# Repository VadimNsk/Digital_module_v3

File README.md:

# Digital_module_v3
Цифровой модуль управления

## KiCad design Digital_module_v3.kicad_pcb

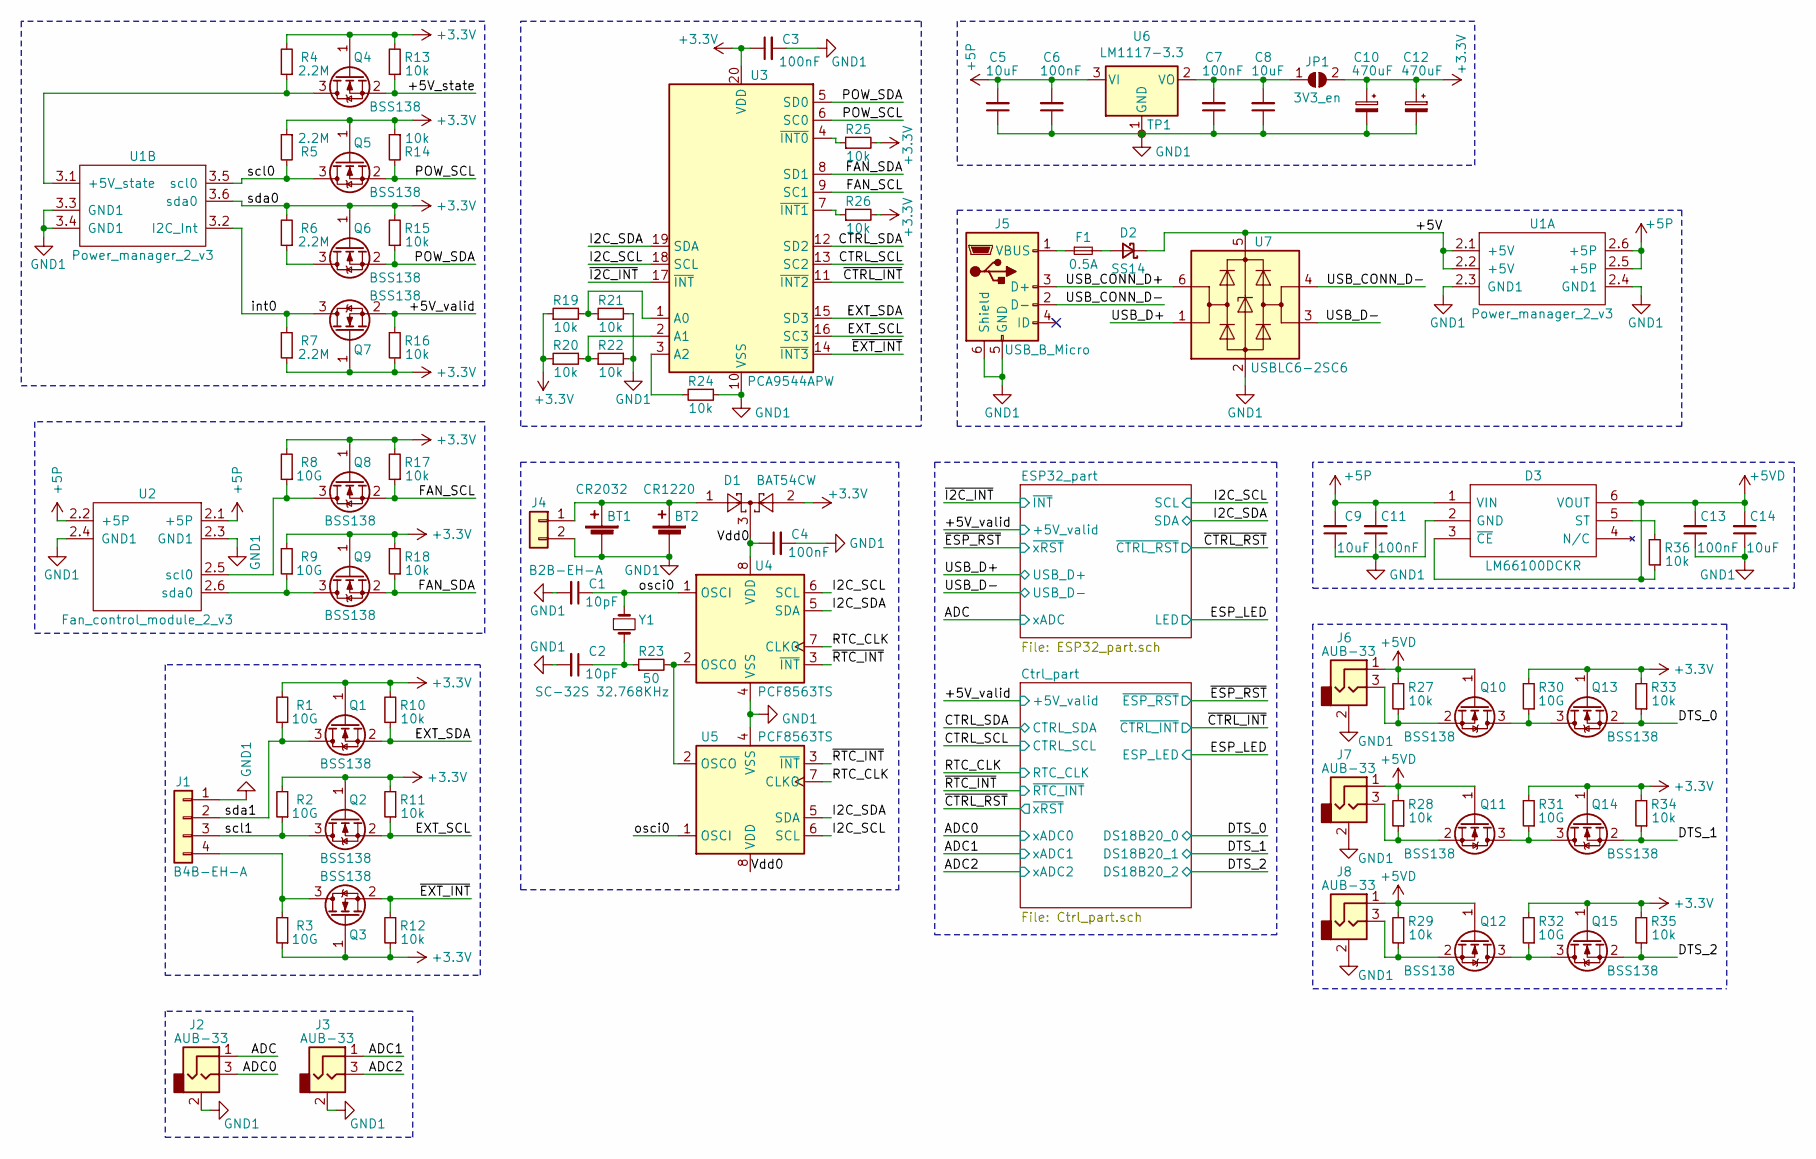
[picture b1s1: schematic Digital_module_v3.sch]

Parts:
BT1: CR2032; CR2032BS51
BT2: CR1220; CR1220HSMD
C1, C2: 10pF; C_0603_1608Metric
C3, C4, C6, C7, C11, C13: 100nF; C_0603_1608Metric
C5, C8, C9, C14: 10uF; C_0603_1608Metric
C10, C12: 470uF; CP_EIA-7343-31_Kemet-D
D1: BAT54CW; SOT-323_SC-70
D2: SS14; D_SMA
D3: LM66100DCKR; SOP65P210X110-6N; Manufacturer_Part_Number LM66100DCKR; Mouser Part Number 595-LM66100DCKR
F1: 0.5A; Fuse_1206_3216Metric
J1: B4B-EH-A; JST_EH_S4B-EH_1x04_P2.50mm_Horizontal
J2, J3, J6, J7, J8: AUB-33
J4: B2B-EH-A; JST_EH_S2B-EH_1x02_P2.50mm_Horizontal
J5: USB_B_Micro; USB_Micro-B_Wuerth_629105150521
JP1: 3V3_en; SolderJumper-2_P1.3mm_Open_TrianglePad1.0x1.5mm
Q1, Q2, Q3, Q4, Q5, Q6, Q7, Q8, Q9, Q10, Q11, Q12, Q13, Q14, Q15: BSS138; SOT-23
R1, R2, R3, R8, R9, R30, R31, R32: 10G; R_0603_1608Metric
R4, R5, R6, R7: 2.2M; R_0603_1608Metric
R10, R11, R12, R13, R14, R15, R16, R17, R18, R19, R20, R21, R22, R24, R25, R26, R27, R28, R29, R33, R34, R35, R36: 10k; R_0603_1608Metric
R23: 50; R_0603_1608Metric
TP1: GND1; TestPoint_THTPad_D2.0mm_Drill1.0mm
U1: Power_manager_2_v3
U2: Fan_control_module_2_v3; Fan_controller_2_v3
U3: PCA9544APW; TSSOP-20_4.4x6.5mm_P0.65mm
U4: PCF8563TS; SOT65P490X110-8N
U5: PCF8563TS; SO-8_3.9x4.9mm_P1.27mm
U6: LM1117-3.3; SOT-223-3_TabPin2
U7: USBLC6-2SC6; SOT-23-6
Y1: SC-32S 32.768KHz; Crystal_SMD_3215-2Pin_3.2x1.5mm

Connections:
+3V3: C3.1, C10.1, C12.1, D1.2, JP1.2 (B), Q1.1 (G), Q2.1 (G), Q3.1 (G), Q4.1 (G), Q5.1 (G), Q6.1 (G), Q7.1 (G), Q8.1 (G), Q9.1 (G), Q13.1 (G), Q14.1 (G), Q15.1 (G), R1.2, R2.2, R3.1, R4.2, R5.1, R6.2, R7.1, R8.2, R9.2, R10.2, R11.2, R12.1, R13.2, R14.1, R15.2, R16.1, R17.2, R18.2, R19.1, R20.1, R25.2, R26.2, R30.2, R31.2, R32.2, R33.2, R34.2, R35.2, U1.3.6 (sda0), U3.20 (VDD); also elsewhere on the board
+5P: C5.2, C6.2, C9.2, C11.2, D3.1 (VIN), U1.2.5 (+5P), U1.2.6 (+5P), U2.2.1 (+5P), U2.2.2 (+5P), U6.3 (VI); also elsewhere on the board
+5VD: C13.2, C14.2, D3.3 (~CE), D3.6 (VOUT), J6.1, J7.1, J8.1, Q10.1 (G), Q11.1 (G), Q12.1 (G), R27.2, R28.2, R29.2, R36.1
/+5V: D2.1 (K), U1.2.1 (+5V), U1.2.2 (+5V), U7.5 (VBUS)
/+5V_state: Q4.2 (S), R13.1
/+5V_valid: Q7.2 (S), R16.2; also elsewhere on the board
/ADC: J2.1; also elsewhere on the board
/ADC0: J2.3; also elsewhere on the board
/ADC1: J3.1; also elsewhere on the board
/ADC2: J3.3; also elsewhere on the board
/CTRL_SCL: U3.13 (SC2); also elsewhere on the board
/CTRL_SDA: U3.12 (SD2); also elsewhere on the board
/DTS_0: Q13.2 (S), R33.1; also elsewhere on the board
/DTS_1: Q14.2 (S), R34.1; also elsewhere on the board
/DTS_2: Q15.2 (S), R35.1; also elsewhere on the board
/EXT_SCL: Q2.2 (S), R11.1, U3.16 (SC3)
/EXT_SDA: Q1.2 (S), R10.1, U3.15 (SD3)
/FAN_SCL: Q8.2 (S), R17.1, U3.9 (SC1)
/FAN_SDA: Q9.2 (S), R18.1, U3.8 (SD1)
/I2C_SCL: U3.18 (SCL), U4.6 (SCL), U5.6 (SCL); also elsewhere on the board
/I2C_SDA: U3.19 (SDA), U4.5 (SDA), U5.5 (SDA); also elsewhere on the board
/POW_SCL: Q5.2 (S), R14.2, U3.6 (SC0)
/POW_SDA: Q6.2 (S), R15.1, U3.5 (SD0)
/RTC_CLK: U4.7 (CLKO), U5.7 (CLKO); also elsewhere on the board
/USB_CONN_D+: J5.3 (D+), U7.6 (I/O1)
/USB_CONN_D-: J5.2 (D-), U7.4 (I/O2)
/USB_D+: U7.1 (I/O1); also elsewhere on the board
/USB_D-: U7.3 (I/O2); also elsewhere on the board
/Vdd0: C4.1, D1.3, U4.8 (VDD), U5.8 (VDD)
/int0: Q7.3 (D), R7.2, U1.3.2 (I2C_Int)
/osci0: C1.1, U4.1 (OSCI), U5.1 (OSCI), Y1.1
/scl0: Q5.3 (D), R5.2, U1.3.5 (scl0)
/scl1: J1.3, Q2.3 (D), R2.1
/sda1: J1.2, Q1.3 (D), R1.1
/~CTRL_INT: U3.11 (~INT2); also elsewhere on the board
/~EXT_INT: Q3.2 (S), R12.2, U3.14 (~INT3)
/~I2C_INT: U3.17 (~INT); also elsewhere on the board
/~RTC_INT: U4.3 (~INT~), U5.3 (~INT~); also elsewhere on the board
GND1: BT1.2 (-), BT2.2 (-), C1.2, C2.2, C3.2, C4.2, C5.1, C6.1, C7.1, C8.1, C9.1, C10.2, C11.1, C12.2, C13.1, C14.1, D3.2 (GND), J1.1, J2.2, J3.2, J4.2, J5.5 (GND), J5.6 (Shield), J6.2, J7.2, J8.2, R21.2, R22.2, R24.1, TP1.1, U1.2.3 (GND1), U1.2.4 (GND1), U1.3.3 (GND1), U1.3.4 (GND1), U2.2.3 (GND1), U2.2.4 (GND1), U3.10 (VSS), U4.4 (VSS), U5.4 (VSS), U6.1 (GND), U7.2 (GND); also elsewhere on the board
unnamed: BT1.1 (+), BT2.1 (+), D1.1, J4.1
unnamed: C2.1, R23.1, Y1.2
unnamed: C7.2, C8.2, JP1.1 (A), U6.2 (VO)
unnamed: D2.2 (A), F1.2
unnamed: D3.5 (ST), R36.2
unnamed: F1.1, J5.1 (VBUS)
unnamed: J1.4, Q3.3 (D), R3.2
unnamed: J6.3, Q10.2 (S), R27.1
unnamed: J7.3, Q11.2 (S), R28.1
unnamed: J8.3, Q12.2 (S), R29.1
unnamed: Q4.3 (D), R4.1, U1.3.1 (+5V_state)
unnamed: Q6.3 (D), R6.1
unnamed: Q8.3 (D), R8.1, U2.2.5 (scl0)
unnamed: Q9.3 (D), R9.1, U2.2.6 (sda0)
unnamed: Q10.3 (D), Q13.3 (D), R30.1
unnamed: Q11.3 (D), Q14.3 (D), R31.1
unnamed: Q12.3 (D), Q15.3 (D), R32.1
unnamed: R19.2, R21.1, U3.1 (A0)
unnamed: R20.2, R22.1, U3.2 (A1)
unnamed: R23.2, U4.2 (OSCO), U5.2 (OSCO)
unnamed: R24.2, U3.3 (A2)
unnamed: R25.1, U3.4 (~INT0)
unnamed: R26.1, U3.7 (~INT1)

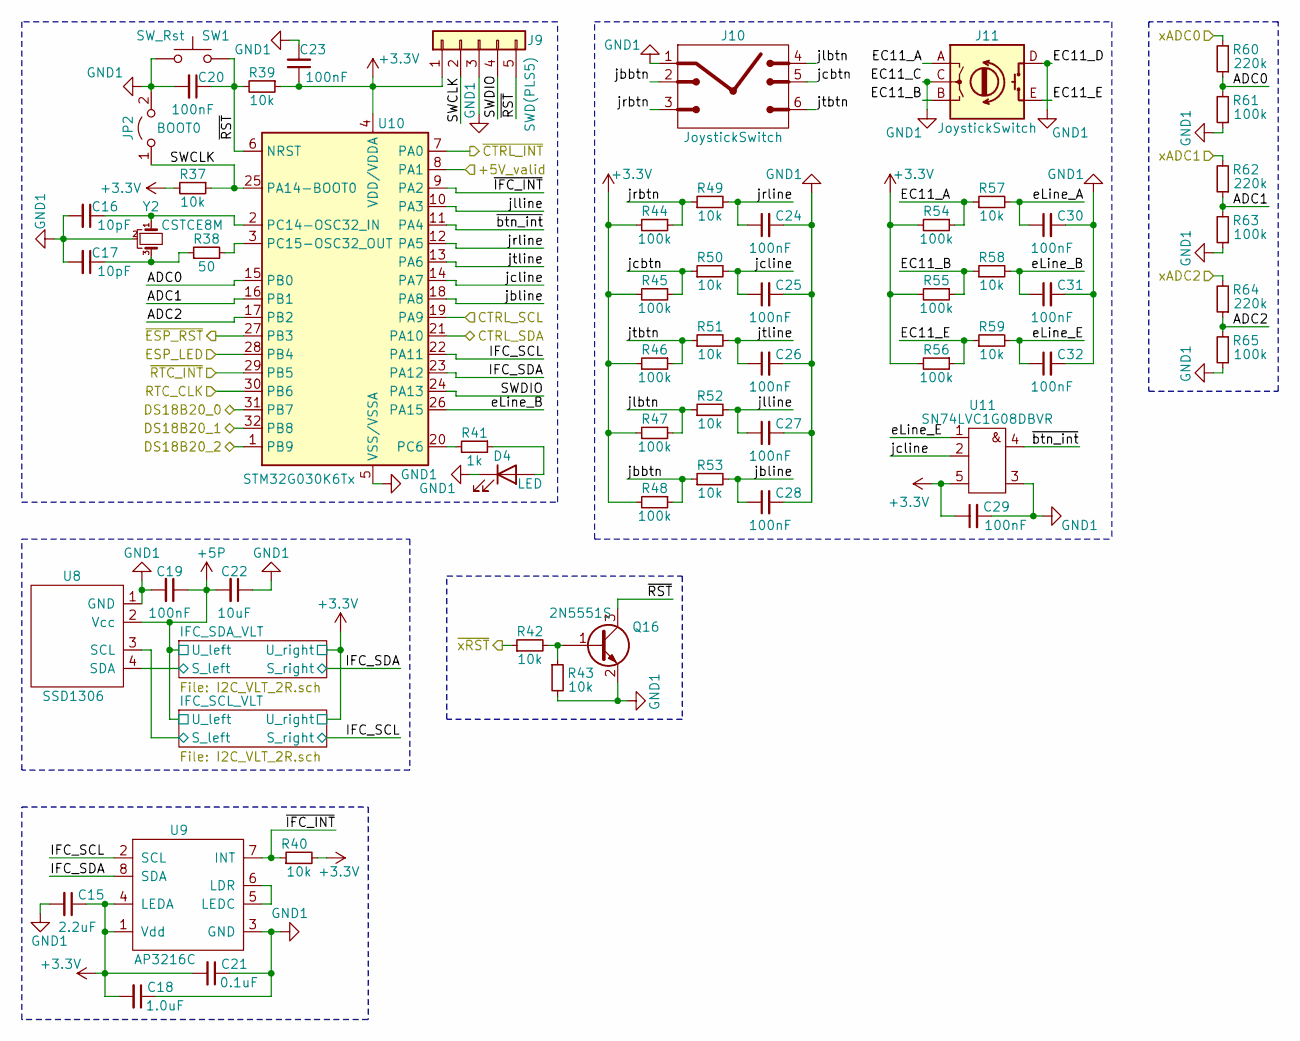
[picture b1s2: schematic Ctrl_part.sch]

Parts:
C15: 2.2uF; C_0603_1608Metric
C16, C17: 10pF; C_0603_1608Metric
C18: 1.0uF; C_0603_1608Metric
C19, C20, C23, C24, C25, C26, C27, C28, C29, C30, C31, C32: 100nF; C_0603_1608Metric
C21: 0.1uF; C_0603_1608Metric
C22: 10uF; C_0603_1608Metric
D4: LED; LED_0603_1608Metric
J9: SWD(PLS5); PinSocket_1x05_P1.27mm_Vertical_SMD_Pin1Left
J10: JoystickSwitch
J11: JoystickSwitch; EC11_SMD
JP2: BOOT0; PinHeader_1x02_P1.27mm_Vertical
Q16: 2N5551S; SOT-23
R37, R39, R40, R42, R43, R49, R50, R51, R52, R53, R57, R58, R59: 10k; R_0603_1608Metric
R38: 50; R_0603_1608Metric
R41: 1k; R_0603_1608Metric
R44, R45, R46, R47, R48, R54, R55, R56, R61, R63, R65: 100k; R_0603_1608Metric
R60, R62, R64: 220k; R_0603_1608Metric
SW1: SW_Rst; SW_SPST_EVQP7C
U8: SSD1306; SSD1306_2_I2C
U9: AP3216C
U10: STM32G030K6Tx; LQFP-32_7x7mm_P0.8mm
U11: SN74LVC1G08DBVR; SOT-23-5
Y2: CSTCE8M; Resonator_SMD_muRata_CSTxExxV-3Pin_3.0x1.1mm_HandSoldering

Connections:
+3V3: C15.1, C18.2, C21.2, C23.1, C29.1, J9.1, R37.2, R39.1, R40.2, R44.2, R45.2, R46.2, R47.2, R48.2, R54.2, R55.2, R56.2, U9.1 (Vdd), U9.4 (LEDA), U10.4 (VDD/VDDA), U11.5 (VCC); also elsewhere on the board
+5P: C19.1, C22.2, U8.2 (Vcc); also elsewhere on the board
/+5V_valid: U10.8 (PA1); also elsewhere on the board
/ADC0: R60.2; also elsewhere on the board
/ADC1: R62.2; also elsewhere on the board
/ADC2: R64.2; also elsewhere on the board
/CTRL_SCL: U10.19 (PA9); also elsewhere on the board
/CTRL_SDA: U10.21 (PA10); also elsewhere on the board
/Ctrl_part/ADC0: R60.1, R61.2, U10.15 (PB0)
/Ctrl_part/ADC1: R62.1, R63.2, U10.16 (PB1)
/Ctrl_part/ADC2: R64.1, R65.2, U10.17 (PB2)
/Ctrl_part/EC11_A: J11.A, R54.1, R57.1
/Ctrl_part/EC11_B: J11.B, R55.1, R58.1
/Ctrl_part/EC11_E: J11.E, R56.1, R59.1
/Ctrl_part/IFC_SCL: U9.2 (SCL), U10.22 (PA11); also elsewhere on the board
/Ctrl_part/IFC_SCL_VLT/S_left: U8.3 (SCL); also elsewhere on the board
/Ctrl_part/IFC_SDA: U9.8 (SDA), U10.23 (PA12); also elsewhere on the board
/Ctrl_part/IFC_SDA_VLT/S_left: U8.4 (SDA); also elsewhere on the board
/Ctrl_part/SWCLK: J9.2, JP2.1 (A), R37.1, U10.25 (PA14-BOOT0)
/Ctrl_part/SWDIO: J9.4, U10.24 (PA13)
/Ctrl_part/eLine_A: C30.1, R57.2
/Ctrl_part/eLine_B: C31.1, R58.2, U10.26 (PA15)
/Ctrl_part/eLine_E: C32.1, R59.2, U11.1
/Ctrl_part/jbbtn: J10.2, R48.1, R53.1
/Ctrl_part/jbline: C28.1, R53.2, U10.18 (PA8)
/Ctrl_part/jcbtn: J10.5, R45.1, R50.1
/Ctrl_part/jcline: C25.1, R50.2, U10.14 (PA7), U11.2
/Ctrl_part/jlbtn: J10.4, R47.1, R52.1
/Ctrl_part/jlline: C27.1, R52.2, U10.10 (PA3)
/Ctrl_part/jrbtn: J10.3, R44.1, R49.1
/Ctrl_part/jrline: C24.1, R49.2, U10.12 (PA5)
/Ctrl_part/jtbtn: J10.6, R46.1, R51.1
/Ctrl_part/jtline: C26.1, R51.2, U10.13 (PA6)
/Ctrl_part/~IFC_INT: R40.1, U9.7 (INT), U10.9 (PA2)
/Ctrl_part/~RST: C20.1, J9.5, Q16.3 (C), R39.2, SW1.2, U10.6 (NRST)
/Ctrl_part/~btn_int: U10.11 (PA4), U11.4
/DTS_0: U10.31 (PB7); also elsewhere on the board
/DTS_1: U10.32 (PB8); also elsewhere on the board
/DTS_2: U10.1 (PB9); also elsewhere on the board
/ESP_LED: U10.28 (PB4); also elsewhere on the board
/RTC_CLK: U10.30 (PB6); also elsewhere on the board
/~CTRL_INT: U10.7 (PA0); also elsewhere on the board
/~CTRL_RST: R42.1; also elsewhere on the board
/~ESP_RST: U10.27 (PB3); also elsewhere on the board
/~RTC_INT: U10.29 (PB5); also elsewhere on the board
GND1: C15.2, C16.2, C17.2, C18.1, C19.2, C20.2, C21.1, C22.1, C23.2, C24.2, C25.2, C26.2, C27.2, C28.2, C29.2, C30.2, C31.2, C32.2, D4.1 (K), J9.3, J10.1, J11.C, J11.D, JP2.2 (B), Q16.2 (E), R43.2, R61.1, R63.1, R65.1, SW1.1, U8.1 (GND), U9.3 (GND), U10.5 (VSS/VSSA), U11.3 (GND), Y2.2; also elsewhere on the board
unnamed: C16.1, U10.2 (PC14-OSC32_IN), Y2.1
unnamed: C17.1, R38.1, Y2.3
unnamed: D4.2 (A), R41.1
unnamed: Q16.1 (B), R42.2, R43.1
unnamed: R38.2, U10.3 (PC15-OSC32_OUT)
unnamed: R41.2, U10.20 (PC6)
unnamed: U9.5 (LEDC), U9.6 (LDR)

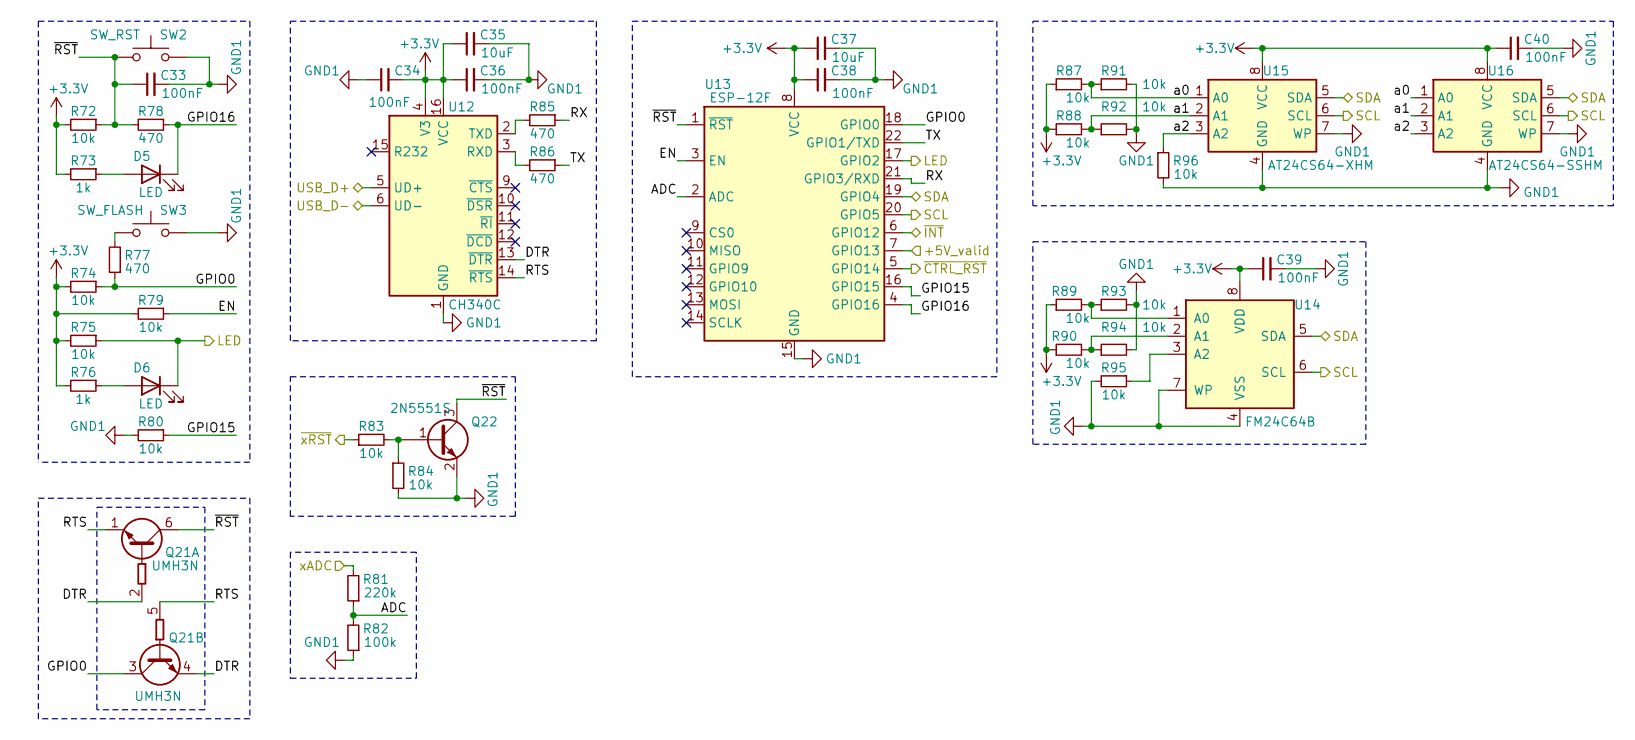
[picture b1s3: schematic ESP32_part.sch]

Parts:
C33, C34, C36, C38, C39, C40: 100nF; C_0603_1608Metric
C35, C37: 10uF; C_0603_1608Metric
D5, D6: LED; LED_0603_1608Metric
Q21: UMH3N; SOT-363_SC-70-6
Q22: 2N5551S; SOT-23
R72, R74, R75, R79, R80, R83, R84, R87, R88, R89, R90, R91, R92, R93, R94, R95, R96: 10k; R_0603_1608Metric
R73, R76: 1k; R_0603_1608Metric
R77, R78, R85, R86: 470; R_0603_1608Metric
R81: 220k; R_0603_1608Metric
R82: 100k; R_0603_1608Metric
SW2: SW_RST; SW_SPST_EVQP7C
SW3: SW_FLASH; SW_SPST_EVQP7C
U12: CH340C; SOIC-16_3.9x9.9mm_P1.27mm
U13: ESP-12F; ESP-12E
U14: FM24C64B; SOIC-8_3.9x4.9mm_P1.27mm
U15: AT24CS64-XHM; TSSOP-8_4.4x3mm_P0.65mm
U16: AT24CS64-SSHM; SOIC-8_3.9x4.9mm_P1.27mm

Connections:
+3V3: C34.2, C35.1, C36.1, C37.1, C38.1, C39.1, C40.1, R72.2, R73.2, R74.2, R75.2, R76.2, R79.2, R87.1, R88.1, R89.1, R90.1, U12.4 (V3), U12.16 (VCC), U13.8 (VCC), U14.8 (VDD), U15.8 (VCC), U16.8 (VCC); also elsewhere on the board
/+5V_valid: U13.7 (GPIO13); also elsewhere on the board
/ADC: R81.2; also elsewhere on the board
/ESP32_part/ADC: R81.1, R82.2, U13.2 (ADC)
/ESP32_part/DTR: Q21.2 (B1), Q21.4 (E2), U12.13 (~DTR)
/ESP32_part/EN: R79.1, U13.3 (EN)
/ESP32_part/GPIO0: Q21.3 (C2), R74.1, R77.1, U13.18 (GPIO0)
/ESP32_part/GPIO15: R80.1, U13.16 (GPIO15)
/ESP32_part/GPIO16: D5.1 (K), R78.1, U13.4 (GPIO16)
/ESP32_part/RTS: Q21.1 (E1), Q21.5 (B2), U12.14 (~RTS)
/ESP32_part/RX: R85.1, U13.21 (GPIO3/RXD)
/ESP32_part/TX: R86.1, U13.22 (GPIO1/TXD)
/ESP32_part/a0: R87.2, R91.1, U15.1 (A0), U16.1 (A0)
/ESP32_part/a1: R88.2, R92.1, U15.2 (A1), U16.2 (A1)
/ESP32_part/a2: R96.1, U15.3 (A2), U16.3 (A2)
/ESP32_part/~RST: C33.1, Q21.6 (C1), Q22.3 (C), R72.1, R78.2, SW2.1, U13.1 (~RST)
/ESP_LED: D6.1 (K), R75.1, U13.17 (GPIO2); also elsewhere on the board
/I2C_SCL: U13.20 (GPIO5), U14.6 (SCL), U15.6 (SCL), U16.6 (SCL); also elsewhere on the board
/I2C_SDA: U13.19 (GPIO4), U14.5 (SDA), U15.5 (SDA), U16.5 (SDA); also elsewhere on the board
/USB_D+: U12.5 (UD+); also elsewhere on the board
/USB_D-: U12.6 (UD-); also elsewhere on the board
/~CTRL_RST: U13.5 (GPIO14); also elsewhere on the board
/~ESP_RST: R83.1; also elsewhere on the board
/~I2C_INT: U13.6 (GPIO12); also elsewhere on the board
GND1: C33.2, C34.1, C35.2, C36.2, C37.2, C38.2, C39.2, C40.2, Q22.2 (E), R80.2, R82.1, R84.2, R91.2, R92.2, R93.2, R94.2, R95.2, R96.2, SW2.2, SW3.2, U12.1 (GND), U13.15 (GND), U14.4 (VSS), U14.7 (WP), U15.4 (GND), U15.7 (WP), U16.4 (GND), U16.7 (WP); also elsewhere on the board
unnamed: D5.2 (A), R73.1
unnamed: D6.2 (A), R76.1
unnamed: Q22.1 (B), R83.2, R84.1
unnamed: R77.2, SW3.1
unnamed: R85.2, U12.2 (TXD)
unnamed: R86.2, U12.3 (RXD)
unnamed: R89.2, R93.1, U14.1 (A0)
unnamed: R90.2, R94.1, U14.2 (A1)
unnamed: R95.1, U14.3 (A2)

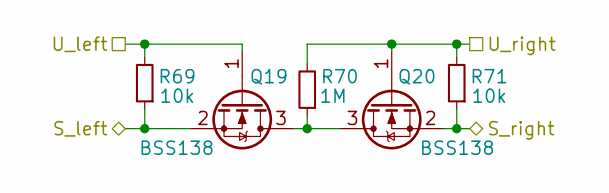
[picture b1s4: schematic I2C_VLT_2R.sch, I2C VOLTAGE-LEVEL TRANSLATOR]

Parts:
Q17, Q18: BSS138; SOT-23
R66, R68: 10k; R_0603_1608Metric
R67: 1M; R_0603_1608Metric

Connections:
+3V3: Q18.1 (G), R67.2, R68.2; also elsewhere on the board
+5P: Q17.1 (G), R66.2; also elsewhere on the board
/Ctrl_part/IFC_SDA: Q18.2 (S), R68.1; also elsewhere on the board
/Ctrl_part/IFC_SDA_VLT/S_left: Q17.2 (S), R66.1; also elsewhere on the board
unnamed: Q17.3 (D), Q18.3 (D), R67.1

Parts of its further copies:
Q19, Q20: BSS138; SOT-23
R69, R71: 10k; R_0603_1608Metric
R70: 1M; R_0603_1608Metric

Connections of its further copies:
+3V3: Q20.1 (G), R70.2, R71.2; also elsewhere on the board
+5P: Q19.1 (G), R69.2; also elsewhere on the board
/Ctrl_part/IFC_SCL: Q20.2 (S), R71.1; also elsewhere on the board
/Ctrl_part/IFC_SCL_VLT/S_left: Q19.2 (S), R69.1; also elsewhere on the board
unnamed: Q19.3 (D), Q20.3 (D), R70.1

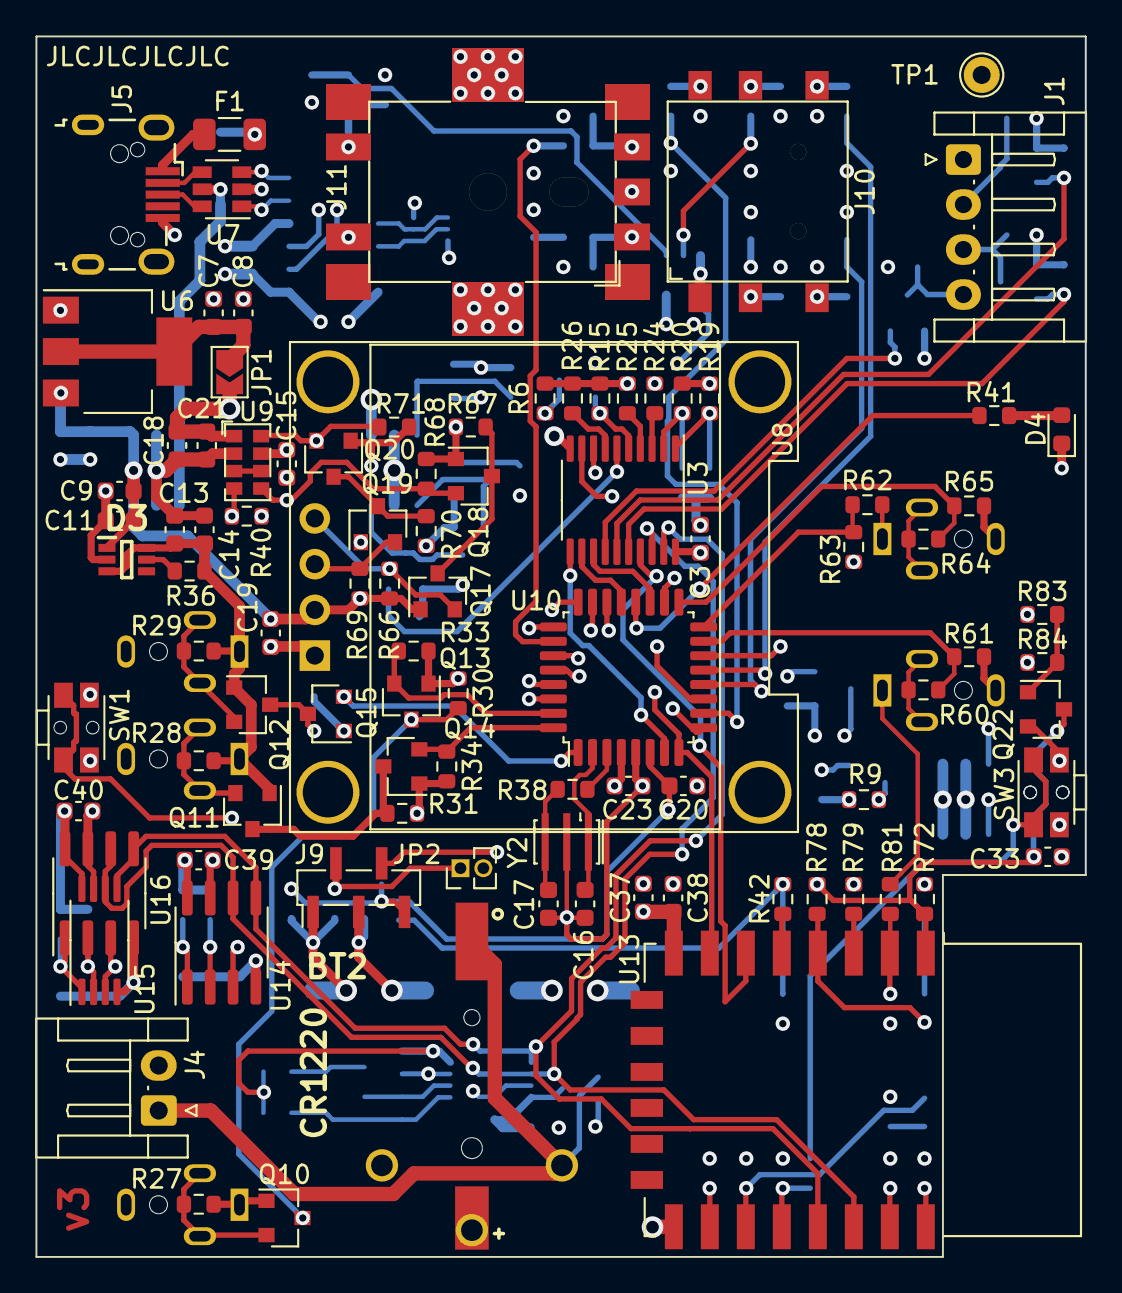
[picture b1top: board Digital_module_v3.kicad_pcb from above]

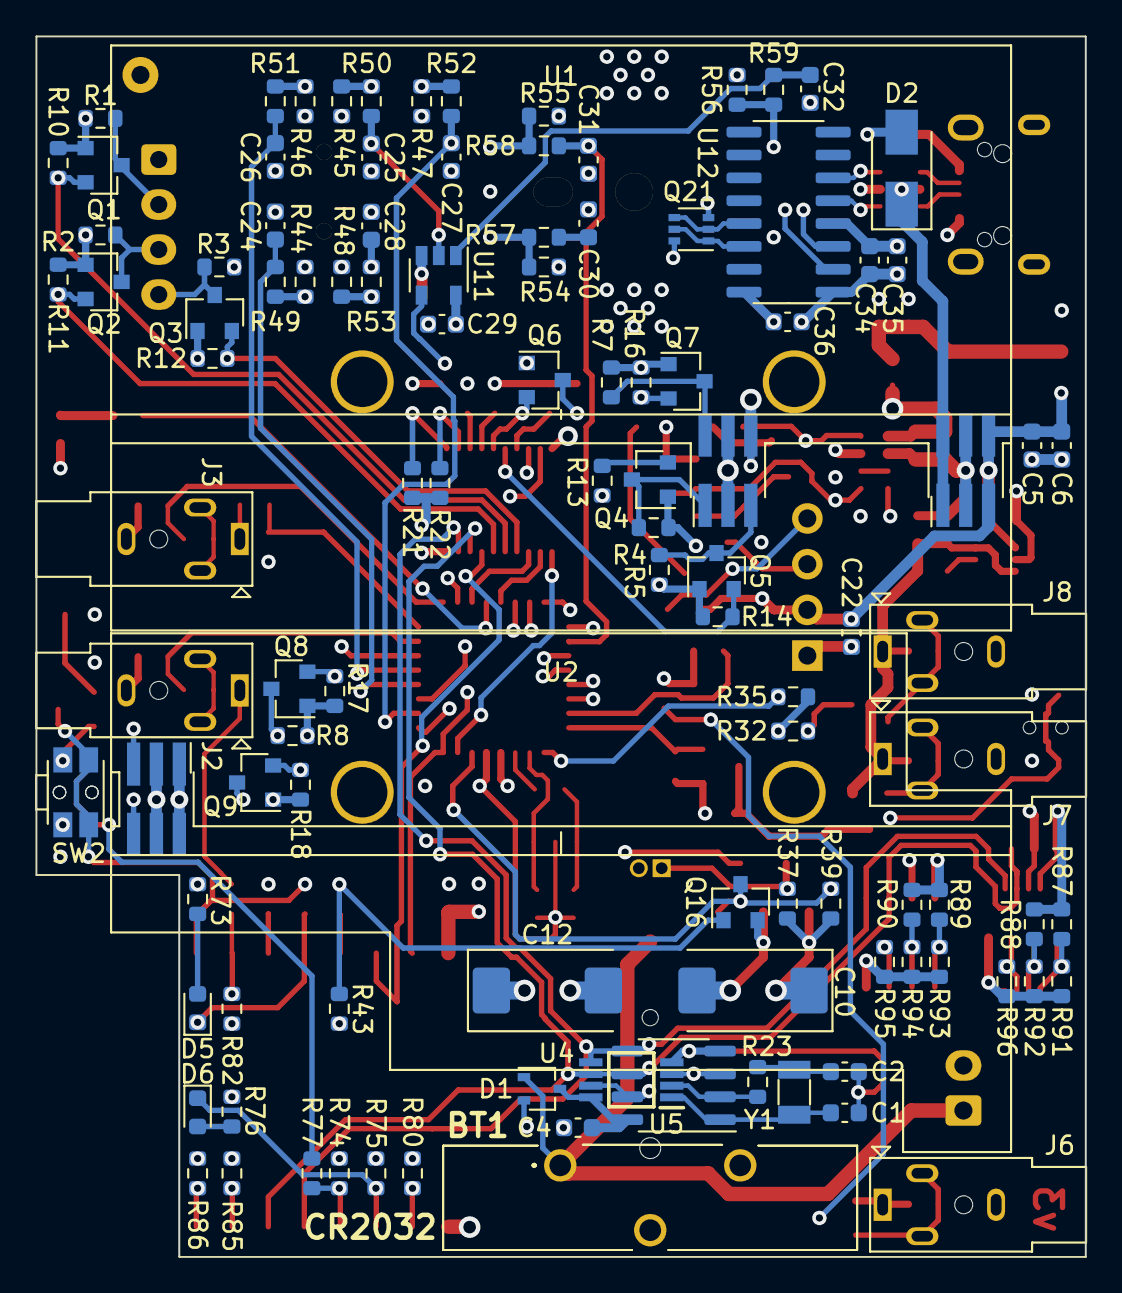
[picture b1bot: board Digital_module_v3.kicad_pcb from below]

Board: 4 copper layers, 58.3 x 67.8 mm, 202 parts (107 on the bottom side), 124 nets.

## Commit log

2021-11-27 Добавлены основные файлы в репозиторий.
2021-11-27 Добавлен список игнорируемых файлов
2022-01-16 Завершена трассировка печатной платы. Исправлены ошибки в схема.
2022-01-18 Добавлен BOM-файл в HTML-формате, гербера и файлы сверловки
2022-01-18 Сформирован перечень элементов, 3D-модель, исправлены ошибки, реализована панелизация платы.
2022-01-19 Добавлен окантовка по контуру платы с двух сторон и текст: "JLCJLCJLCJLC"
2022-02-17 Последние изменения в BOM
